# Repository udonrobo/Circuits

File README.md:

# Circuits
基板のjwデータ / 外注基板データ置き場

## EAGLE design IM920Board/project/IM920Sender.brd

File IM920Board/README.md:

# IM920Board

IM920モジュールを使用した920MHz帯通信基板

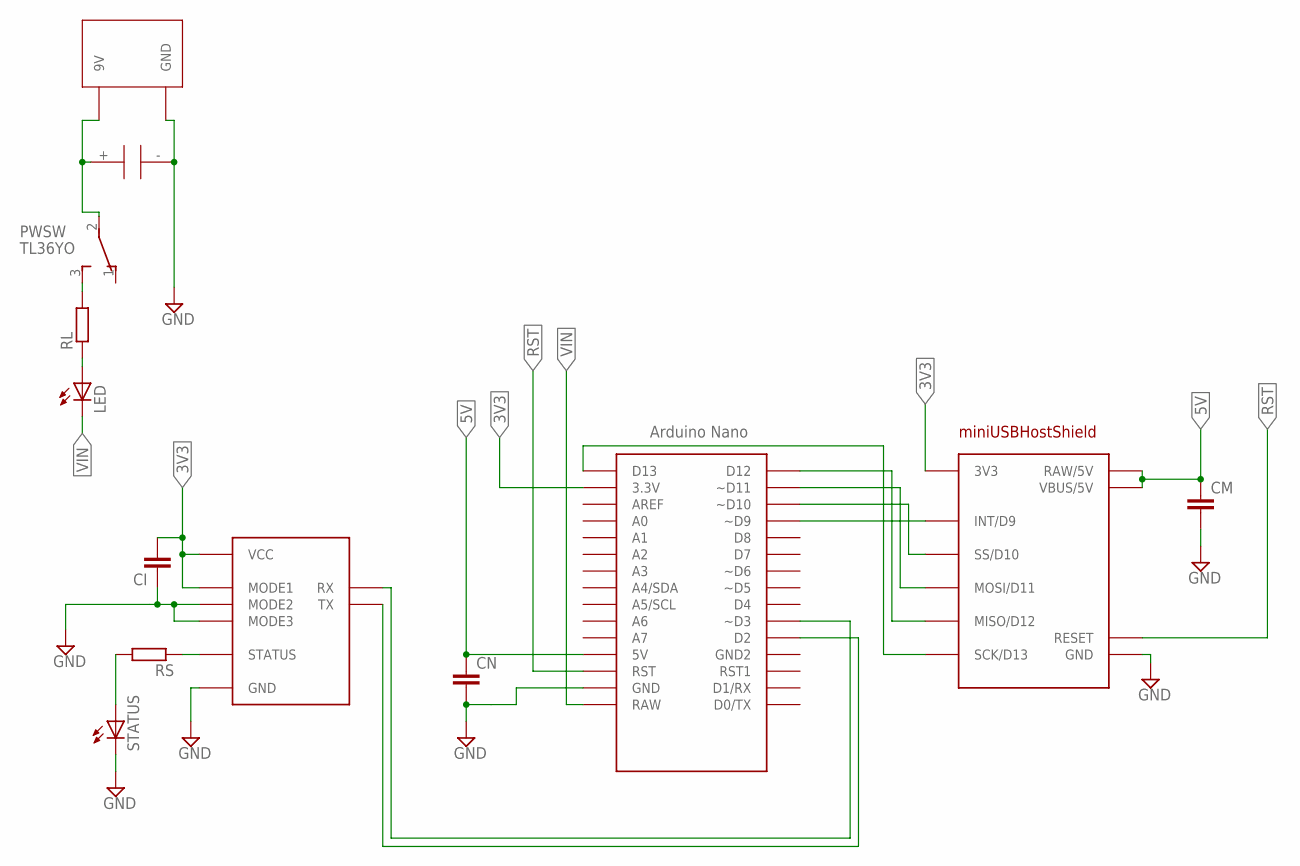
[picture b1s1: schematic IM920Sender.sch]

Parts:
CI: C2.5/2; C2.5-2
CM: C2.5/2; C2.5-2
CN: C2.5/2; C2.5-2
LED: LED3MM
PWSW: TL36YO; TL3XYO
RL: R-EU_0204/7; 0204/7
RS: R-EU_0204/7; 0204/7
STATUS: LED3MM
U$1: IM920
U$2: BH-9V-1P
U$4: MINI-USBHOSTSHIELD; USBMINI
U$5: C-10U
U$6: NANO

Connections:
3V3: CI.2, U$1.MODE1, U$1.VCC, U$4.3V3, U$6.3.3V
5V: CM.1, CN.1, U$4.RAW (RAW/5V), U$4.VBUS (VBUS/5V), U$6.5V
GND: CI.1, CM.2, CN.2, STATUS.K (C), U$1.GND, U$1.MODE2, U$1.MODE3, U$2.GND, U$4.GND, U$4.GND1 (GND), U$5.-, U$6.GND
unnamed: RS.2, STATUS.A
unnamed: RS.1, U$1.STATUS
unnamed: PWSW.2, U$2.9V, U$5.+
unnamed: U$1.TX, U$6.D2
unnamed: U$4.INT (INT/D9), U$6.D9 (~D9)
unnamed: U$4.SS (SS/D10), U$6.D10 (~D10)
unnamed: U$4.MOSI (MOSI/D11), U$6.D11 (~D11)
unnamed: PWSW.3 (S), RL.2
unnamed: U$4.MISO (MISO/D12), U$6.D12
unnamed: LED.A, RL.1
unnamed: U$4.SCK (SCK/D13), U$6.D13
unnamed: U$1.RX, U$6.D3 (~D3)
RST: U$4.RESET, U$6.RST
VIN: LED.K (C), U$6.RAW

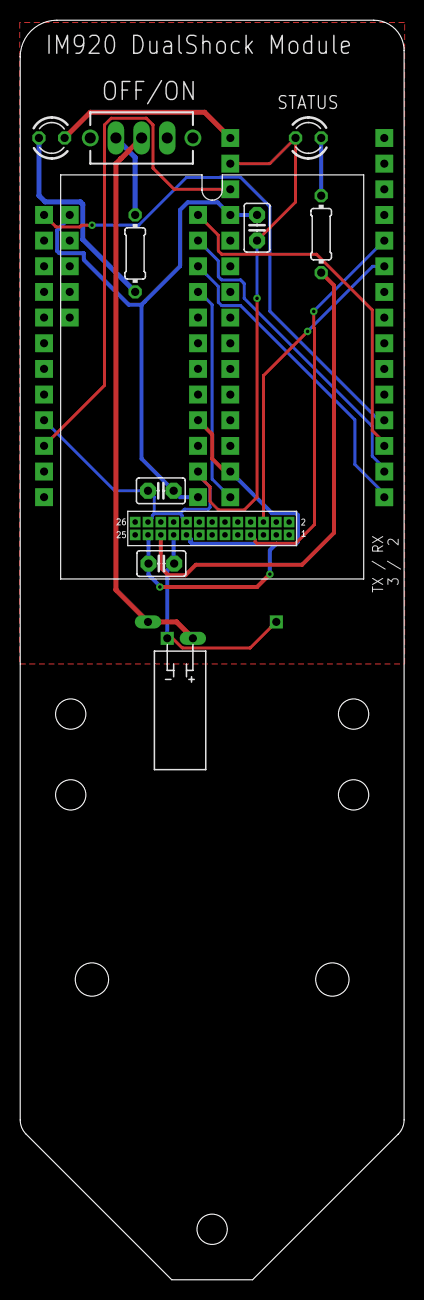
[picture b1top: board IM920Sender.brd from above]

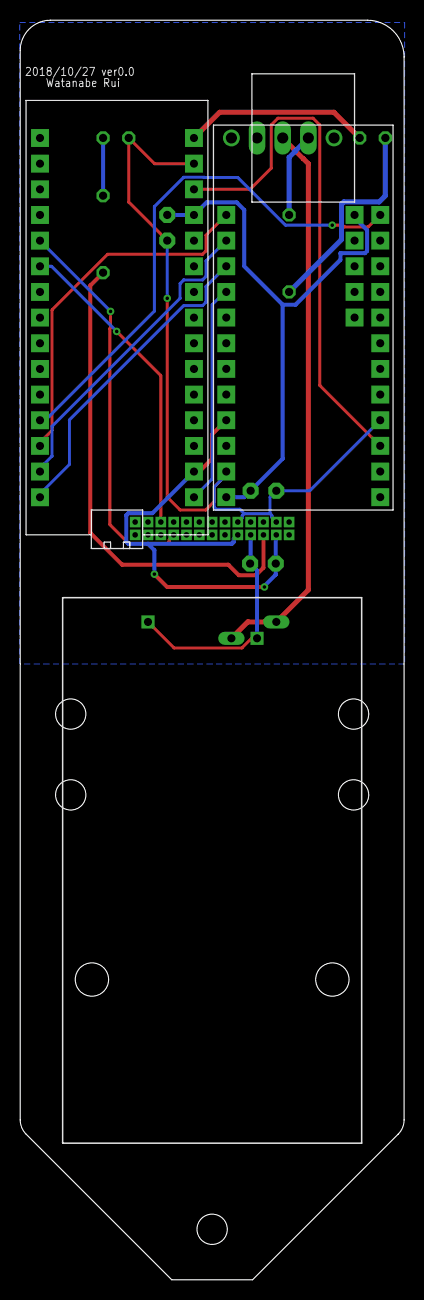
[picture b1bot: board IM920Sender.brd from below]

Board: 2 copper layers, 38.0 x 124.7 mm, 13 parts (3 on the bottom side), 17 nets.

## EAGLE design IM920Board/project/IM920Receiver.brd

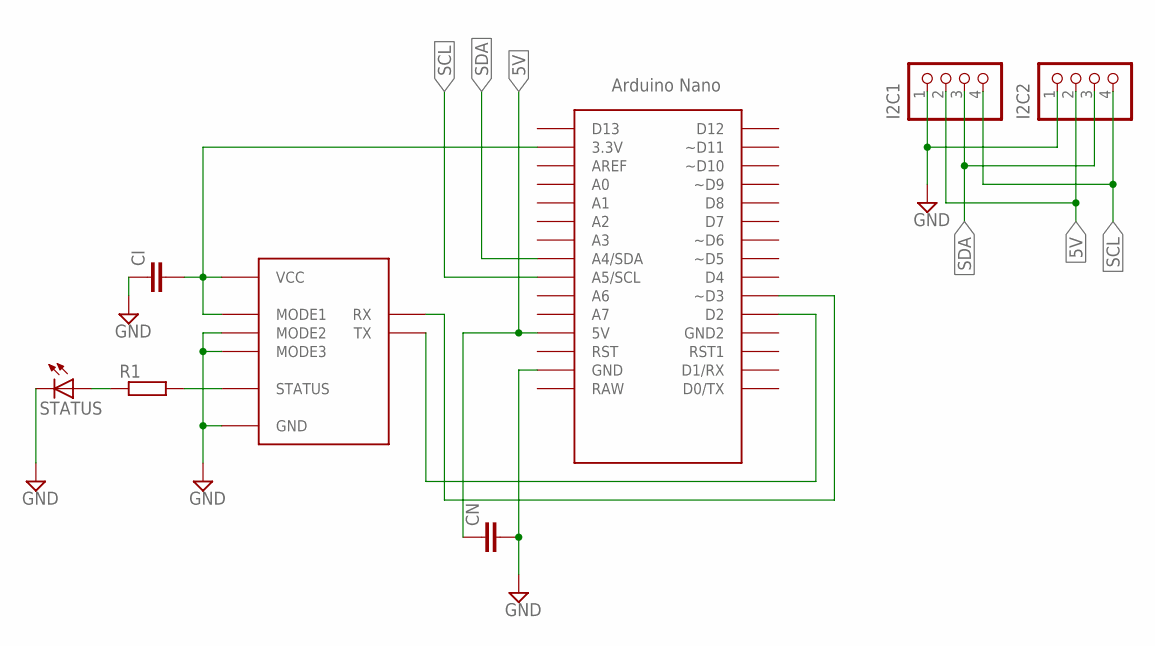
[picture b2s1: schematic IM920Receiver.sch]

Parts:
CI: C2.5/2; C2.5-2
CN: C2.5/2; C2.5-2
I2C1, I2C2: B4B-XH-A
R1: R-EU_0204/7; 0204/7
STATUS: LED3MM
U$1: IM920
U$2: NANO

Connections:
5V: CN.1, I2C1.2, I2C2.2, U$2.5V
GND: CI.1, CN.2, I2C1.1, I2C2.1, STATUS.K (C), U$1.GND, U$1.MODE2, U$1.MODE3, U$2.GND
unnamed: U$1.TX, U$2.D2
unnamed: U$1.RX, U$2.D3 (~D3)
unnamed: CI.2, U$1.MODE1, U$1.VCC, U$2.3.3V
unnamed: R1.2, U$1.STATUS
unnamed: R1.1, STATUS.A
SCL: I2C1.4, I2C2.4, U$2.A5 (A5/SCL)
SDA: I2C1.3, I2C2.3, U$2.A4 (A4/SDA)

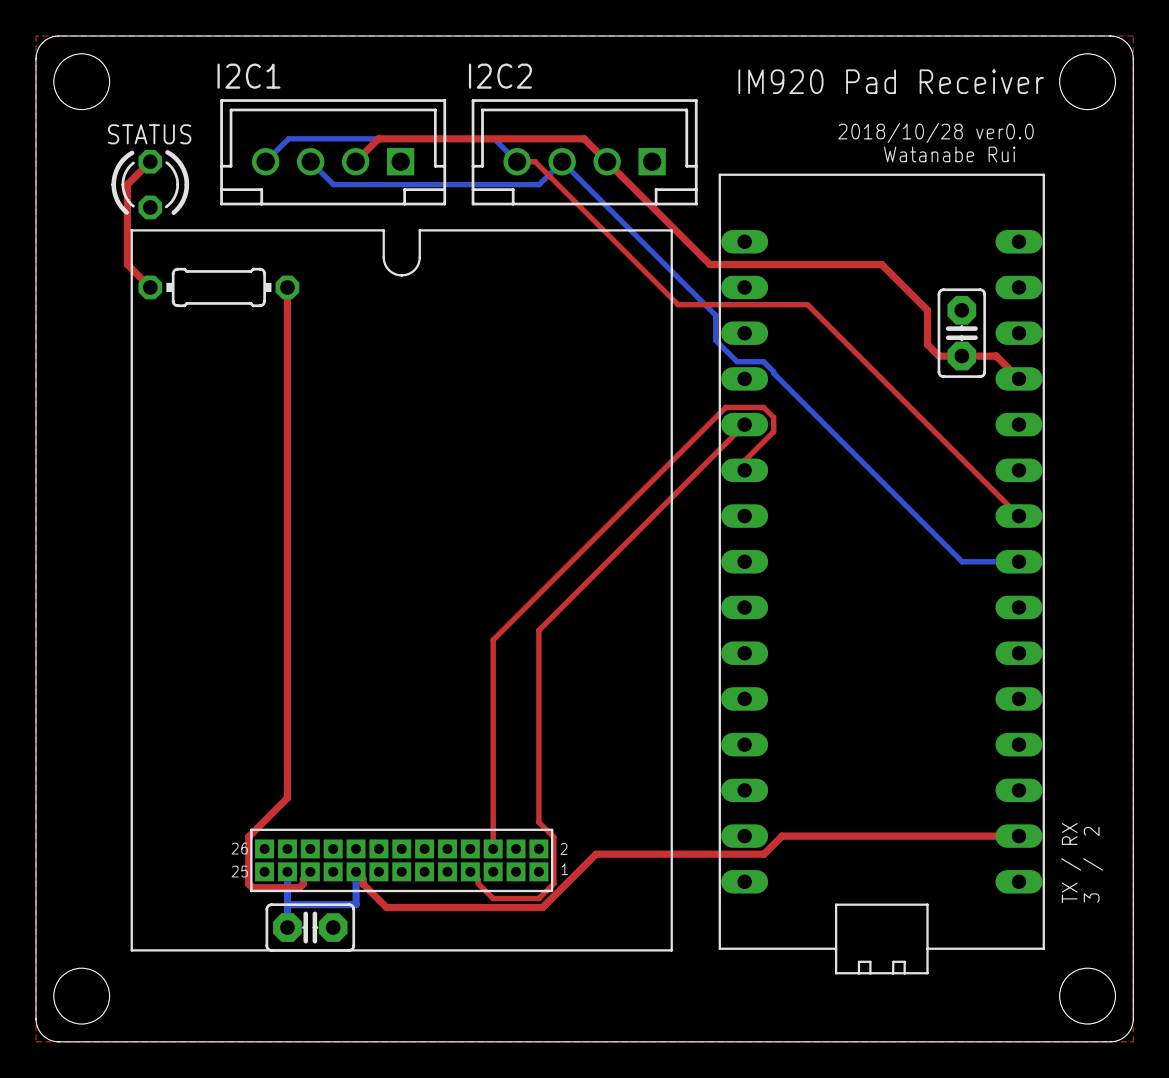
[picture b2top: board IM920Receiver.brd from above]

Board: 2 copper layers, 61.0 x 55.9 mm, 8 parts (0 on the bottom side), 9 nets.

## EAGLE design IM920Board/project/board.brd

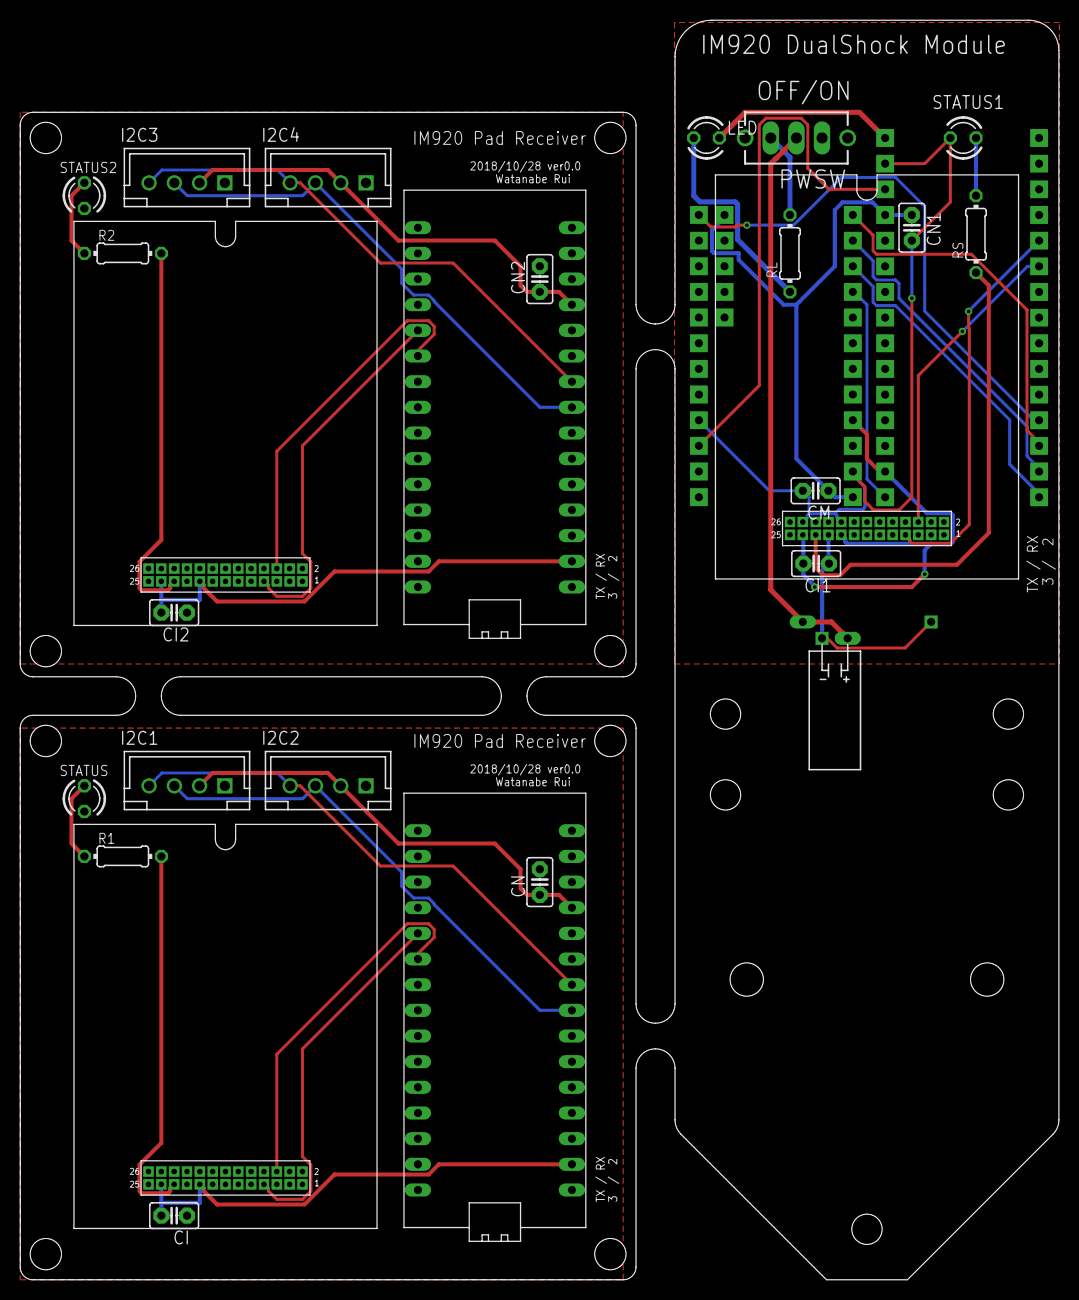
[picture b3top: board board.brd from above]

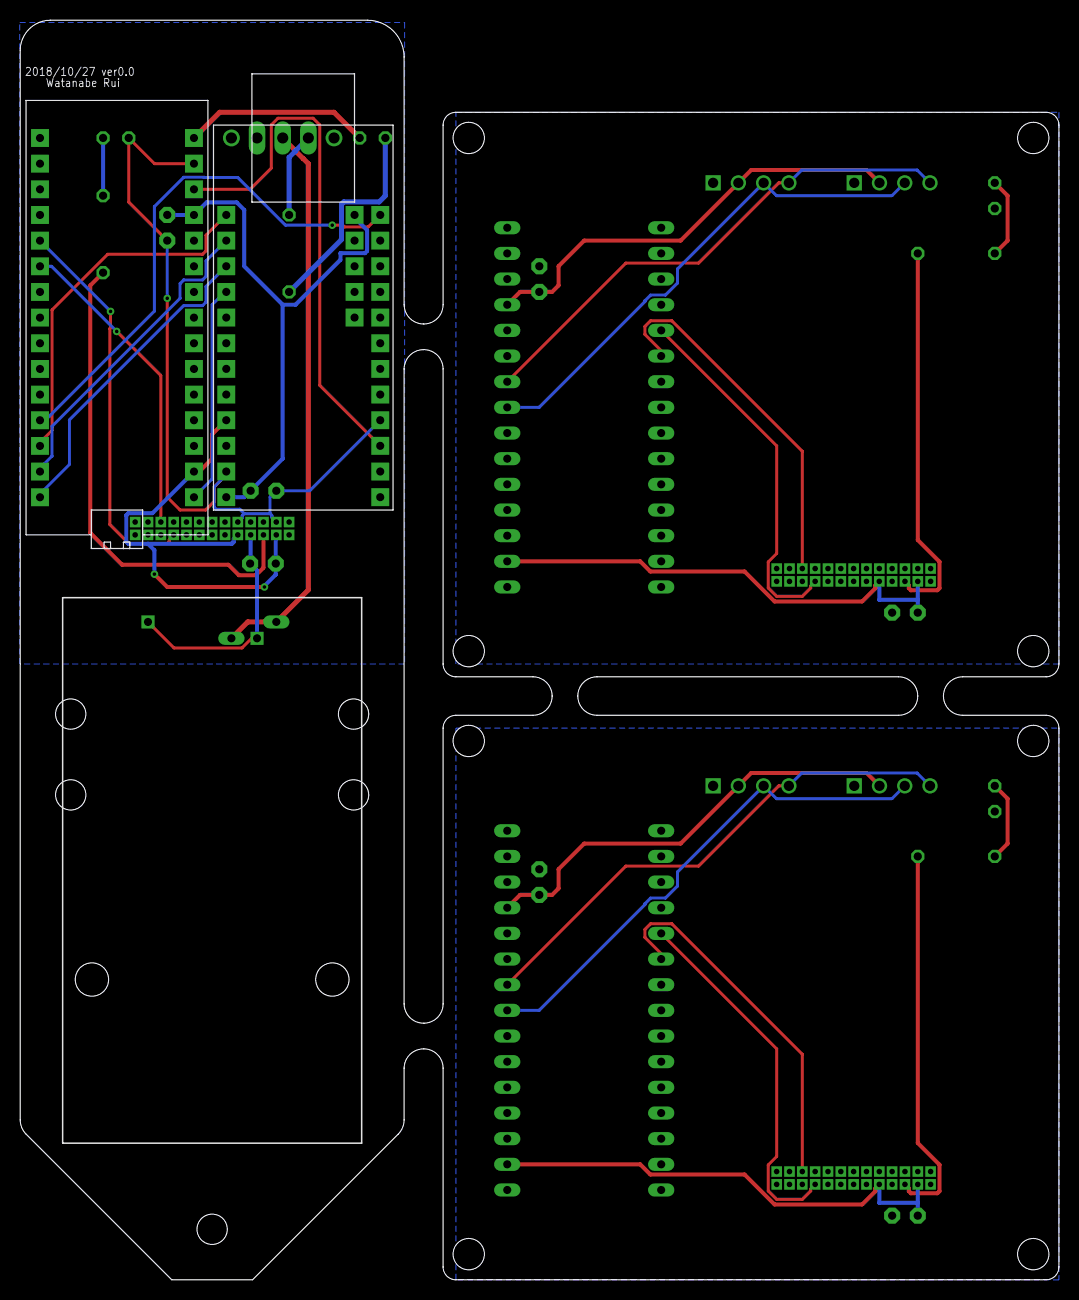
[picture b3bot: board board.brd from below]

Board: 2 copper layers, 102.8 x 124.7 mm, 29 parts (3 on the bottom side), 35 nets.

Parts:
CI, CI1, CI2: C2.5-2
CM: C2.5-2
CN, CN1, CN2: C2.5-2
I2C1, I2C2, I2C3, I2C4: B4B-XH-A
LED: LED3MM
PWSW: TL36YO; TL3XYO
R1, R2: 0204/7
RL: 0204/7
RS: 0204/7
STATUS, STATUS1, STATUS2: LED3MM
U$1, U$3, U$8: IM920
U$2, U$6, U$9: NANO
U$4: MINI-USBHOSTSHIELD; USBMINI
U$5: C-10U
U$7: BH-9V-1P

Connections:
3V3: CI1.2, U$3.MODE1, U$3.VCC, U$4.3V3, U$6.3.3V
5V: CN.1, I2C1.2, I2C2.2, U$2.5V
5V1: CM.1, CN1.1, U$4.RAW, U$4.VBUS, U$6.5V
5V2: CN2.1, I2C3.2, I2C4.2, U$9.5V
GND: CI.1, CN.2, I2C1.1, I2C2.1, STATUS.K, U$1.GND, U$1.MODE2, U$1.MODE3, U$2.GND
GND1: CI1.1, CM.2, CN1.2, STATUS1.K, U$3.GND, U$3.MODE2, U$3.MODE3, U$4.GND, U$4.GND1, U$5.-, U$6.GND, U$7.GND
GND2: CI2.1, CN2.2, I2C3.1, I2C4.1, STATUS2.K, U$8.GND, U$8.MODE2, U$8.MODE3, U$9.GND
unnamed: U$1.TX, U$2.D2
unnamed: U$1.RX, U$2.D3
unnamed: CI.2, U$1.MODE1, U$1.VCC, U$2.3.3V
unnamed: R1.2, U$1.STATUS
unnamed: R1.1, STATUS.A
unnamed: RS.2, STATUS1.A
unnamed: RS.1, U$3.STATUS
unnamed: U$3.TX, U$6.D2
unnamed: PWSW.3, RL.2
unnamed: LED.A, RL.1
unnamed: PWSW.2, U$5.+, U$7.9V
unnamed: U$4.INT, U$6.D9
unnamed: U$4.SS, U$6.D10
unnamed: U$3.RX, U$6.D3
unnamed: U$4.MOSI, U$6.D11
unnamed: U$4.MISO, U$6.D12
unnamed: U$4.SCK, U$6.D13
unnamed: U$8.TX, U$9.D2
unnamed: U$8.RX, U$9.D3
unnamed: CI2.2, U$8.MODE1, U$8.VCC, U$9.3.3V
unnamed: R2.2, U$8.STATUS
unnamed: R2.1, STATUS2.A
RST: U$4.RESET, U$6.RST
SCL: I2C1.4, I2C2.4, U$2.A5
SCL1: I2C3.4, I2C4.4, U$9.A5
SDA: I2C1.3, I2C2.3, U$2.A4
SDA1: I2C3.3, I2C4.3, U$9.A4
VIN: LED.K, U$6.RAW
